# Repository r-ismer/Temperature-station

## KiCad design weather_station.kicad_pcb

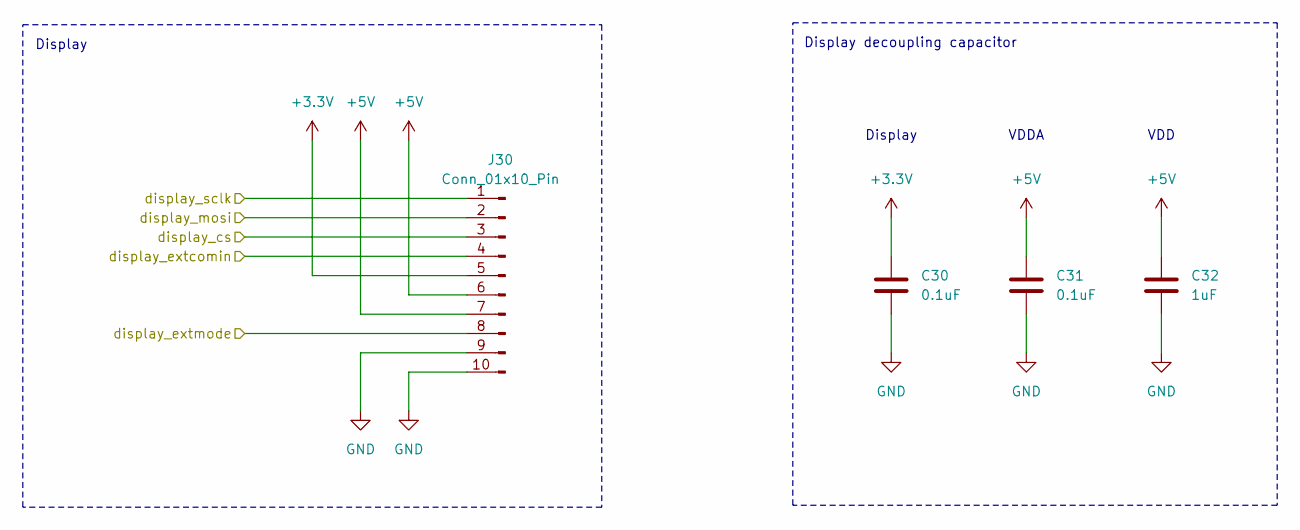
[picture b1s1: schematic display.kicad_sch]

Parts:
C30, C31: 0.1uF; C_0805_2012Metric
C32: 1uF; C_0805_2012Metric
J30: Conn_01x10_Pin; FFC2B35-10-T

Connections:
+3.3V: C30.1, J30.5; also elsewhere on the board
+5V: C31.1, C32.1, J30.6, J30.7; also elsewhere on the board
/Display/display_cs: J30.3; also elsewhere on the board
/Display/display_extcomin: J30.4; also elsewhere on the board
/Display/display_extmode: J30.8; also elsewhere on the board
/Display/display_mosi: J30.2; also elsewhere on the board
/Display/display_sclk: J30.1; also elsewhere on the board
GND: C30.2, C31.2, C32.2, J30.9, J30.10; also elsewhere on the board

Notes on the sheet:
Display decoupling capacitor
Display
VDD
VDDA

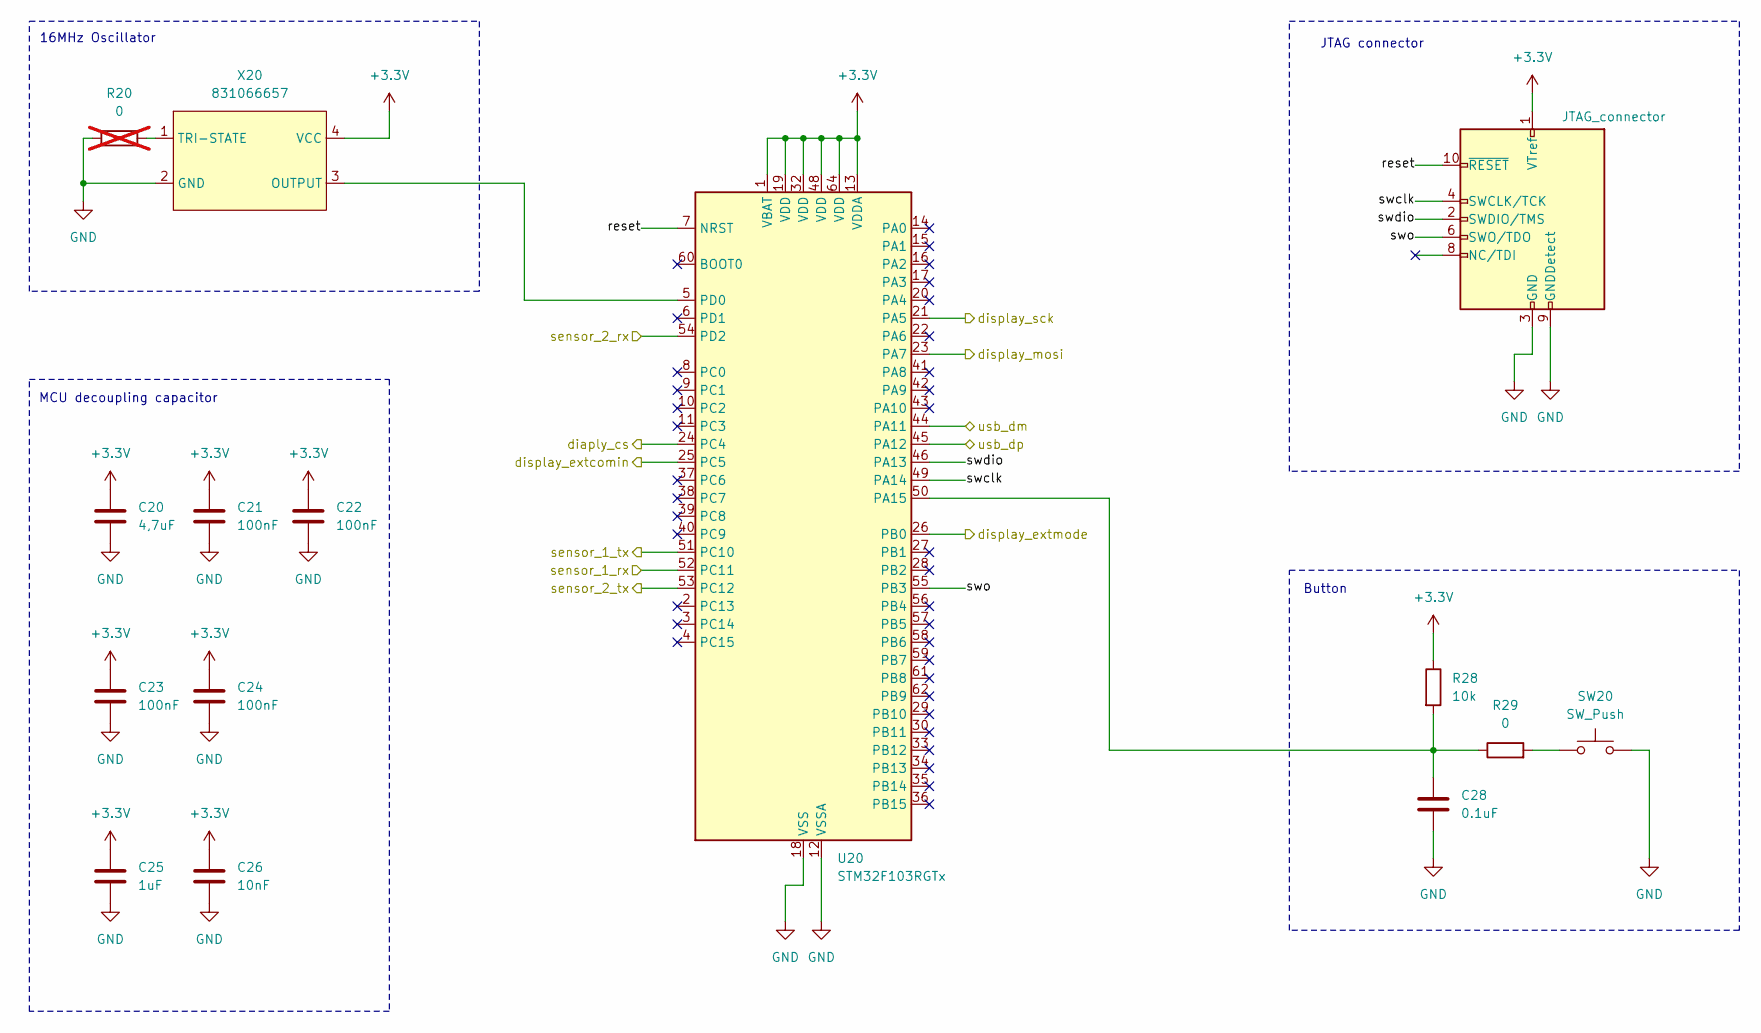
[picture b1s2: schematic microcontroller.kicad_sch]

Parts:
C20: 4,7uF; C_0805_2012Metric
C21, C22, C23, C24: 100nF; C_0805_2012Metric
C25: 1uF; C_0805_2012Metric
C26: 10nF; C_0805_2012Metric
C28: 0.1uF; C_0805_2012Metric
J20: JTAG_connector; 627010021621
R20: 0; R_0805_2012Metric; not fitted
R28: 10k; R_0805_2012Metric
R29: 0; R_0805_2012Metric
SW20: SW_Push; SWT0310
U20: STM32F103RGTx; LQFP-64_10x10mm_P0.5mm
X20: 831066657

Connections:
+3.3V: C20.1, C21.1, C22.1, C23.1, C24.1, C25.1, C26.1, J20.1 (VTref), R28.1, U20.1 (VBAT), U20.13 (VDDA), U20.19 (VDD), U20.32 (VDD), U20.48 (VDD), U20.64 (VDD), X20.4 (VCC); also elsewhere on the board
/Connectors/sensor_1_rx: U20.52 (PC11); also elsewhere on the board
/Connectors/sensor_1_tx: U20.51 (PC10); also elsewhere on the board
/Connectors/sensor_2_rx: U20.54 (PD2); also elsewhere on the board
/Connectors/sensor_2_tx: U20.53 (PC12); also elsewhere on the board
/Connectors/usb_dm: U20.44 (PA11); also elsewhere on the board
/Connectors/usb_dp: U20.45 (PA12); also elsewhere on the board
/Display/display_cs: U20.24 (PC4); also elsewhere on the board
/Display/display_extcomin: U20.25 (PC5); also elsewhere on the board
/Display/display_extmode: U20.26 (PB0); also elsewhere on the board
/Display/display_mosi: U20.23 (PA7); also elsewhere on the board
/Display/display_sclk: U20.21 (PA5); also elsewhere on the board
/Microcontroller/reset: J20.10 (~RESET), U20.7 (NRST)
/Microcontroller/swclk: J20.4 (SWCLK/TCK), U20.49 (PA14)
/Microcontroller/swdio: J20.2 (SWDIO/TMS), U20.46 (PA13)
/Microcontroller/swo: J20.6 (SWO/TDO), U20.55 (PB3)
GND: C20.2, C21.2, C22.2, C23.2, C24.2, C25.2, C26.2, C28.2, J20.3 (GND), J20.5 (GND), J20.9 (GNDDetect), R20.1, SW20.3 (2), U20.12 (VSSA), U20.18 (VSS), U20.31 (VSS), U20.47 (VSS), U20.63 (VSS), X20.2 (GND); also elsewhere on the board
unnamed: R29.2, SW20.1
unnamed: C28.1, R28.2, R29.1, U20.50 (PA15)
unnamed: U20.5 (PD0), X20.3 (OUTPUT)
unnamed: R20.2, X20.1 (TRI-STATE)

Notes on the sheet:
Button
16MHz Oscillator
JTAG connector
MCU decoupling capacitor

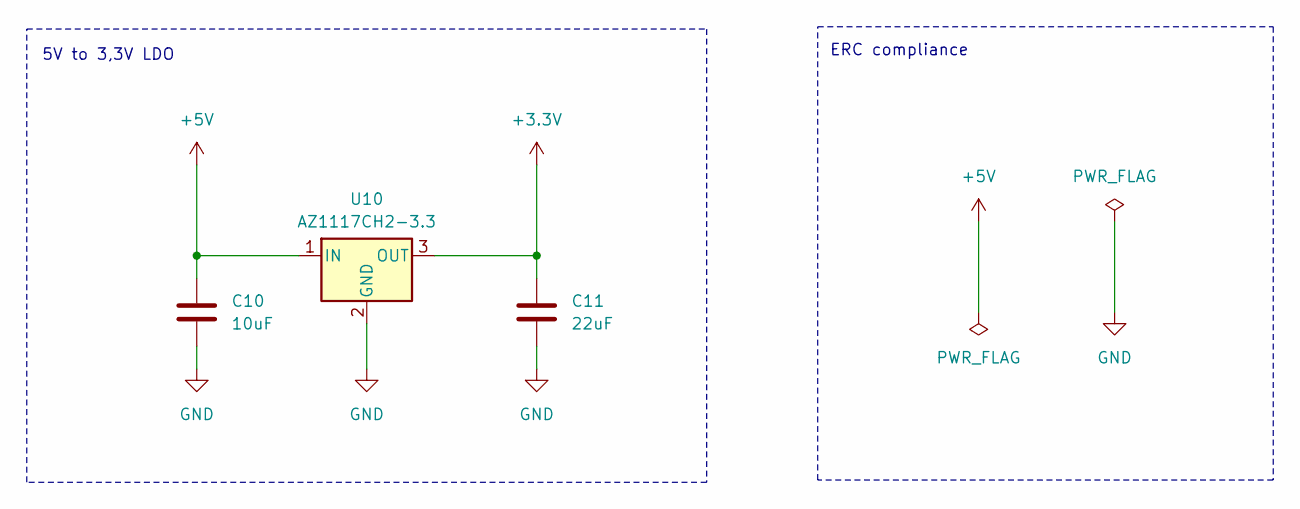
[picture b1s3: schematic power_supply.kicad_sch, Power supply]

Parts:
C10: 10uF; C_0805_2012Metric
C11: 22uF; C_0805_2012Metric
U10: AZ1117CH2-3.3; SOT-223-3_TabPin2

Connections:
+3.3V: C11.1, U10.3 (OUT); also elsewhere on the board
+5V: C10.1, U10.1 (IN); also elsewhere on the board
GND: C10.2, C11.2, U10.2 (GND); also elsewhere on the board

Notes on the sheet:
5V to 3,3V LDO
ERC compliance

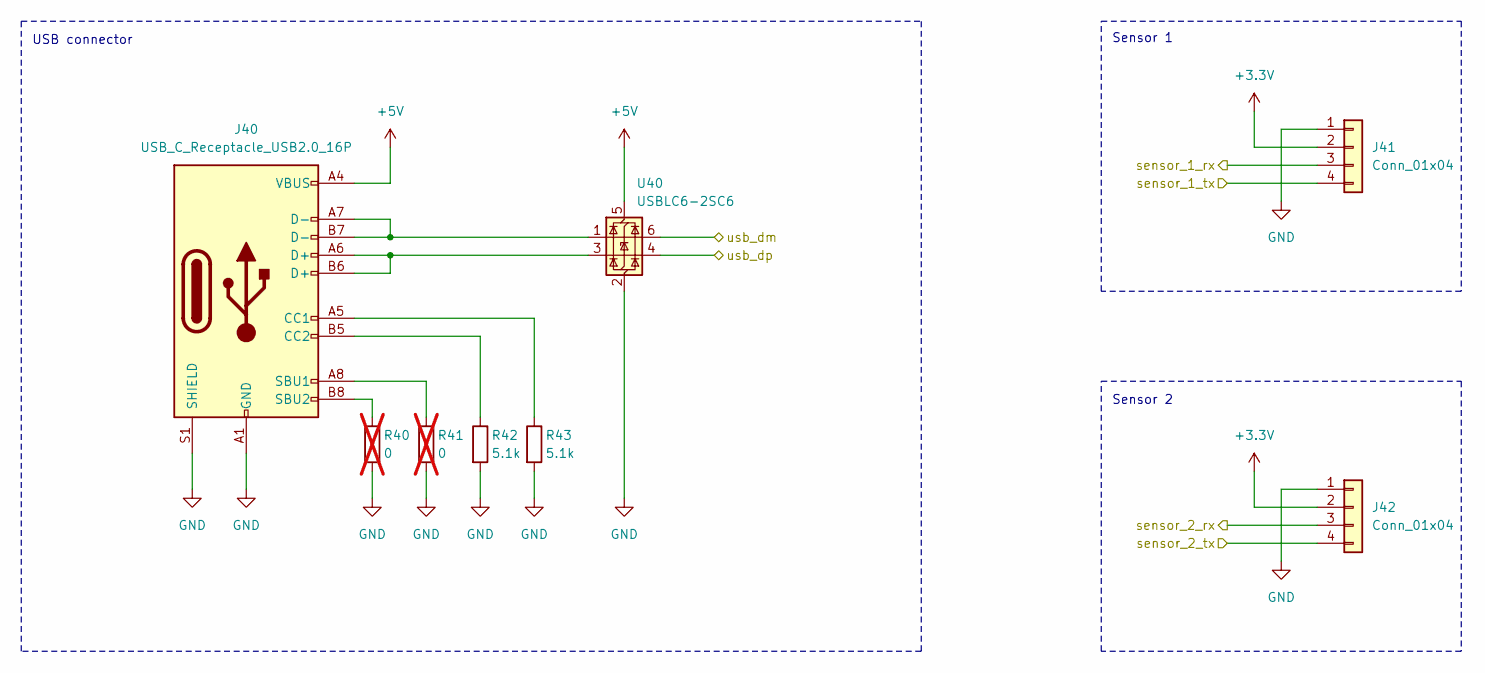
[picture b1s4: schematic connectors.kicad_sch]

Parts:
J40: USB_C_Receptacle_USB2.0_16P; USB_C_Receptacle_GCT_USB4105-xx-A_16P_TopMnt_Horizontal
J41, J42: Conn_01x04; jst_pa4
R40, R41: 0; R_0805_2012Metric; not fitted
R42, R43: 5.1k; R_0805_2012Metric
U40: USBLC6-2SC6; SOT-23-6

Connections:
+3.3V: J41.2, J42.2; also elsewhere on the board
+5V: J40.A4 (VBUS), J40.A9 (VBUS), J40.B4 (VBUS), J40.B9 (VBUS), U40.5 (VBUS); also elsewhere on the board
/Connectors/sensor_1_rx: J41.3; also elsewhere on the board
/Connectors/sensor_1_tx: J41.4; also elsewhere on the board
/Connectors/sensor_2_rx: J42.3; also elsewhere on the board
/Connectors/sensor_2_tx: J42.4; also elsewhere on the board
/Connectors/usb_dm: U40.6 (I/O1); also elsewhere on the board
/Connectors/usb_dp: U40.4 (I/O2); also elsewhere on the board
GND: J40.A1 (GND), J40.A12 (GND), J40.B1 (GND), J40.B12 (GND), J40.S1 (SHIELD), J41.1, J42.1, R40.2, R41.2, R42.2, R43.2, U40.2 (GND); also elsewhere on the board
unnamed: J40.A5 (CC1), R43.1
unnamed: J40.B5 (CC2), R42.1
unnamed: J40.A6 (D+), J40.B6 (D+), U40.3 (I/O2)
unnamed: J40.A7 (D-), J40.B7 (D-), U40.1 (I/O1)
unnamed: J40.A8 (SBU1), R41.1
unnamed: J40.B8 (SBU2), R40.1

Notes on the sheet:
Sensor 2
Sensor 1
USB connector

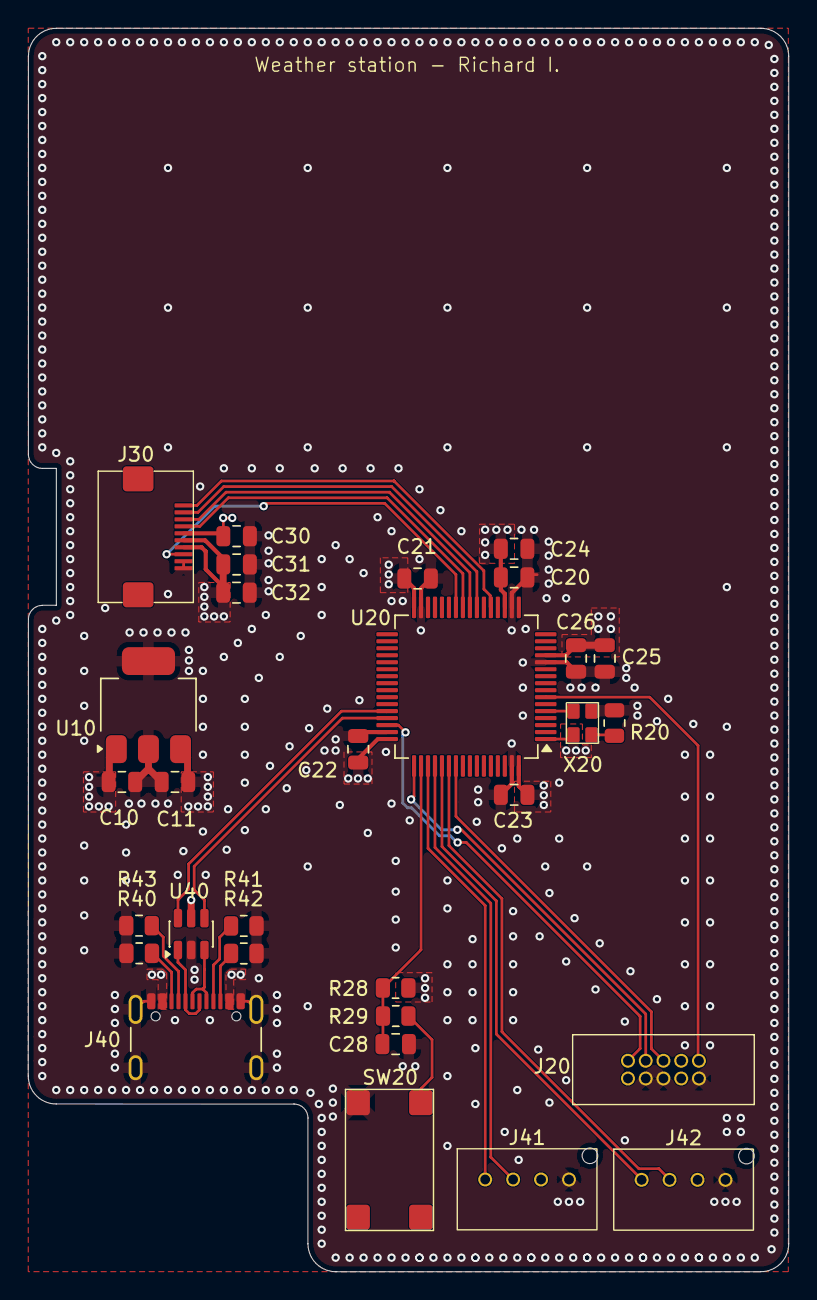
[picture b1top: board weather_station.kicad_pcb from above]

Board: 2 copper layers, 54.4 x 89.0 mm, 30 parts (0 on the bottom side), 28 nets.

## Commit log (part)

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2026-01-22 Updated gitigore
2026-01-22 Removed .prl file
2026-06-27 Finished schematic and first layout
2026-06-28 Added planes in routing
2026-06-30 Created board outline
